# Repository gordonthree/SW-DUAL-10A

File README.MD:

# Smart Switch Node
* Dual BTS7002-1EPP Profet Smart Switches 21a each
* Heavy duty cage-clamp type connectors for power in/out
* Pin-header connections for linking to a can bus control module
* Voltage divider for measuring supply voltage

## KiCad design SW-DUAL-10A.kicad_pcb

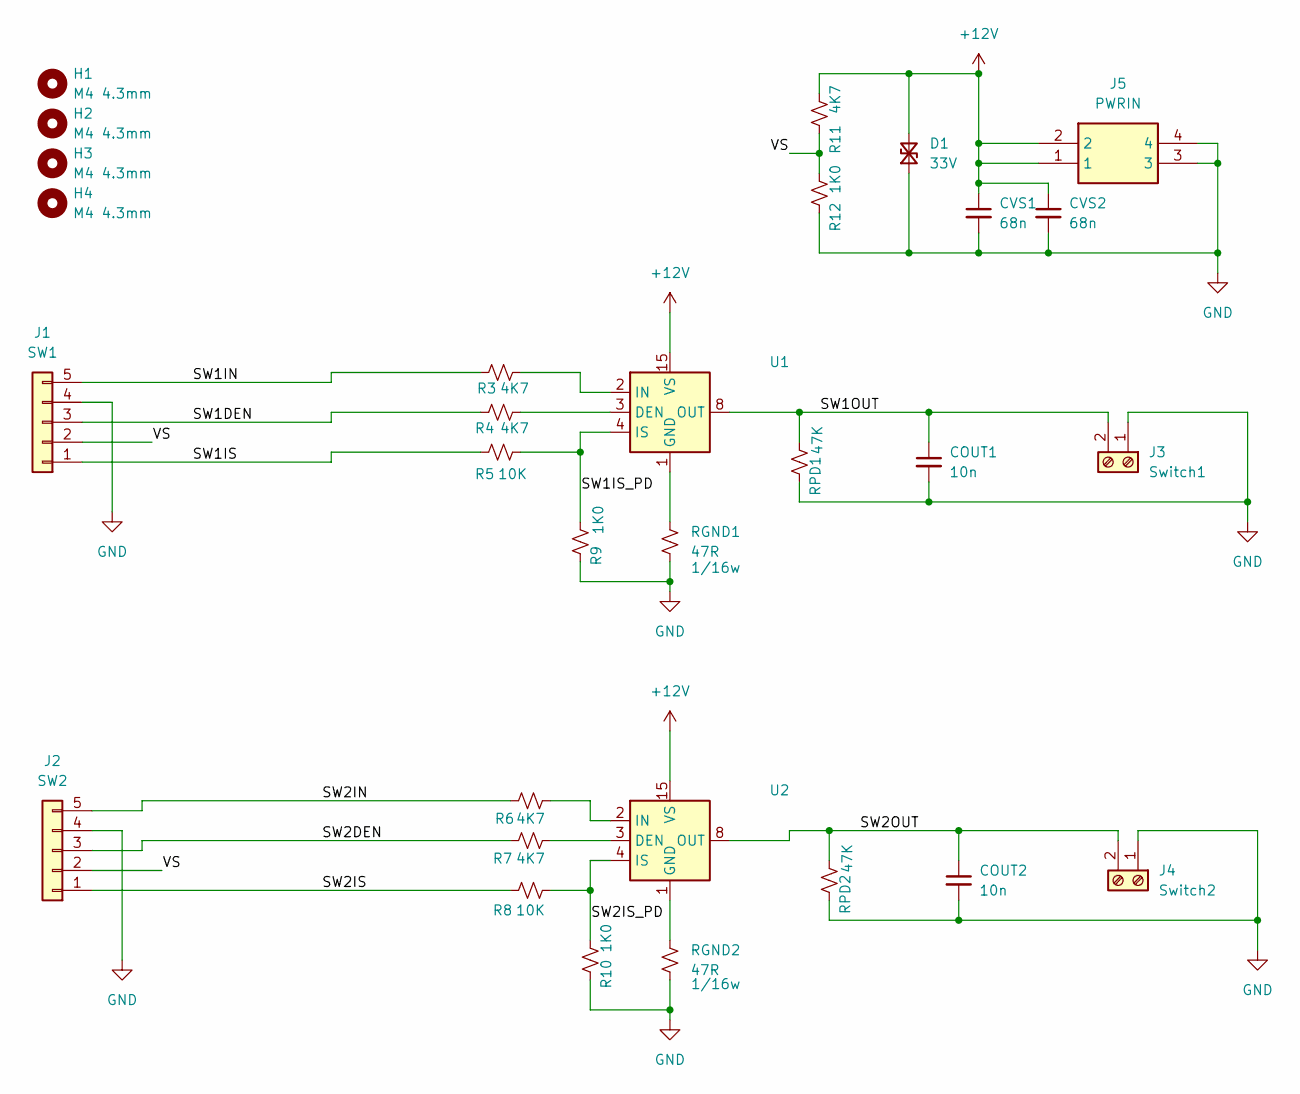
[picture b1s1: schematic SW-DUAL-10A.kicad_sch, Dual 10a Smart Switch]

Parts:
COUT1, COUT2: 10n; C_0603_1608Metric_Pad1.08x0.95mm_HandSolder
CVS1, CVS2: 68n; C_0603_1608Metric_Pad1.08x0.95mm_HandSolder
D1: 33V; D_0603_1608Metric_Pad1.05x0.95mm_HandSolder
H1, H2, H3, H4: M4 4.3mm; MountingHole_4.3mm_M4
J1: SW1; PinHeader_1x05_P2.54mm_Horizontal
J2: SW2; PinHeader_1x05_P2.54mm_Horizontal
J3: Switch1; TerminalBlock_Phoenix_MKDS-1,5-2-5.08_1x02_P5.08mm_Horizont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
J4: Switch2; TerminalBlock_Phoenix_MKDS-1,5-2-5.08_1x02_P5.08mm_Horizont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
J5: PWRIN; VP0265840000G; Mouser Part Number 649-VP02658400J0G
R3, R4, R6, R7: 4K7; R_0603_1608Metric_Pad0.98x0.95mm_HandSolder
R5, R8: 10K; R_0603_1608Metric_Pad0.98x0.95mm_HandSolder
R9, R10: 1K0; R_0603_1608Metric_Pad0.98x0.95mm_HandSolder
R11: 4K7; R_Axial_DIN0207_L6.3mm_D2.5mm_P7.62mm_Horizontal
R12: 1K0; R_Axial_DIN0207_L6.3mm_D2.5mm_P7.62mm_Horizontal
RGND1, RGND2: 47R; R_0603_1608Metric_Pad0.98x0.95mm_HandSolder
RPD1, RPD2: 47K; R_0603_1608Metric_Pad0.98x0.95mm_HandSolder
U1, U2: BTS7002-1EPP; SOP65P600X115-15N

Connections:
+12V: CVS1.1, CVS2.1, D1.2 (A2), J5.1, J5.2, R11.2, U1.15 (VS), U2.15 (VS)
/SW1DEN: J1.3, R4.1
/SW1IN: J1.5, R3.1
/SW1IS: J1.1, R5.1
/SW1IS_PD: R5.2, R9.2, U1.4 (IS)
/SW1OUT: COUT1.1, J3.2, RPD1.2, U1.8 (OUT), U1.9 (OUT), U1.10 (OUT), U1.12 (OUT), U1.13 (OUT), U1.14 (OUT)
/SW2DEN: J2.3, R7.1
/SW2IN: J2.5, R6.1
/SW2IS: J2.1, R8.1
/SW2IS_PD: R8.2, R10.2, U2.4 (IS)
/SW2OUT: COUT2.1, J4.2, RPD2.2, U2.8 (OUT), U2.9 (OUT), U2.10 (OUT), U2.12 (OUT), U2.13 (OUT), U2.14 (OUT)
/VS: J1.2, J2.2, R11.1, R12.2
GND: COUT1.2, COUT2.2, CVS1.2, CVS2.2, D1.1 (A1), J1.4, J2.4, J3.1, J4.1, J5.3, J5.4, R9.1, R10.1, R12.1, RGND1.2, RGND2.2, RPD1.1, RPD2.1
unnamed: R4.2, U1.3 (DEN)
unnamed: RGND1.1, U1.1 (GND)
unnamed: R3.2, U1.2 (IN)
unnamed: R7.2, U2.3 (DEN)
unnamed: RGND2.1, U2.1 (GND)
unnamed: R6.2, U2.2 (IN)

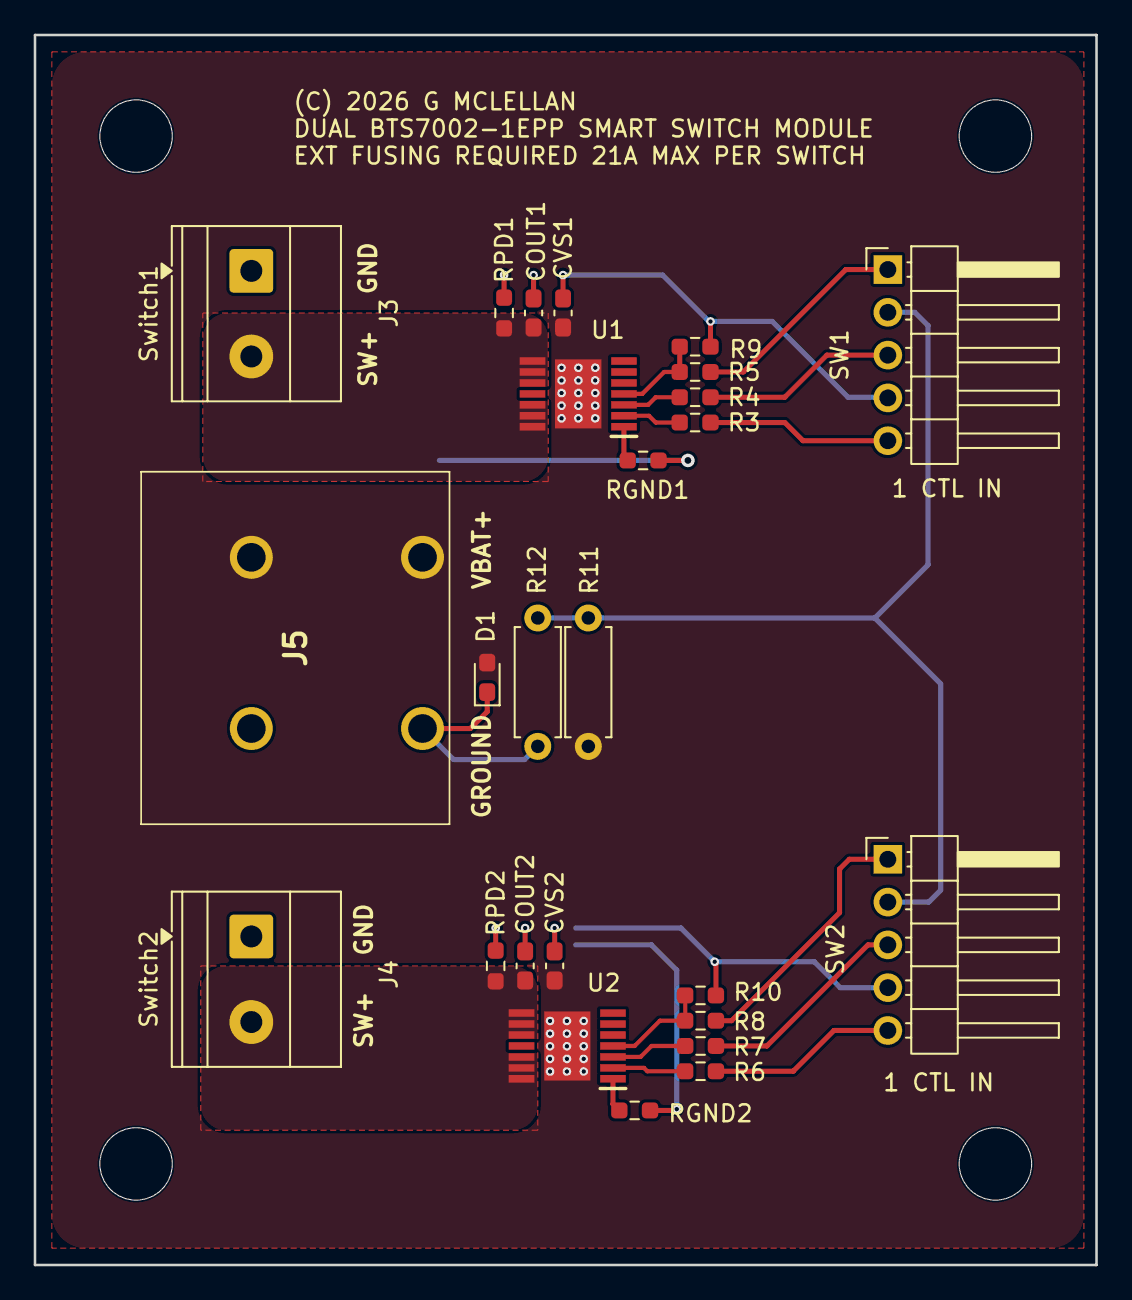
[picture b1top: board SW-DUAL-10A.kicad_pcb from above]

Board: 2 copper layers, 63.0 x 73.0 mm, 30 parts (0 on the bottom side), 19 nets.

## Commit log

2026-01-16 everything is on the layout, needs a lot of tuning
2026-01-17 added some mounting holes, pretty much finished, send it to the fab

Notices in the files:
SW-DUAL-10A.kicad_pcb:
(C) 2026 G MCLELLAN
